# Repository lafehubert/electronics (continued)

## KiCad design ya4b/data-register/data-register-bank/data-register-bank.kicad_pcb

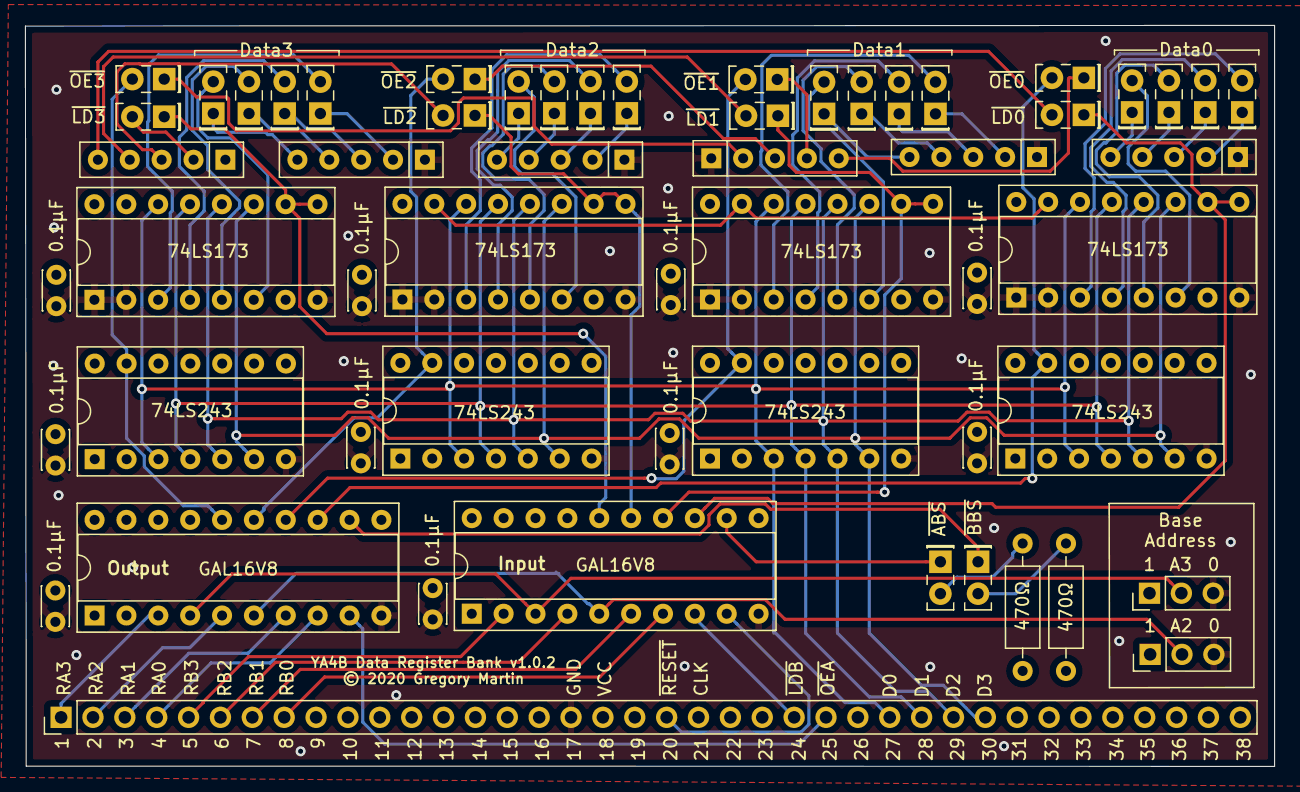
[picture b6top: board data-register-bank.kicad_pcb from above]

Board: 4 copper layers, 99.6 x 59.1 mm, 57 parts (0 on the bottom side), 73 nets.

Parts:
C1, C2, C3, C4, C5, C6, C7, C8, C9, C10: 0.1µF; C_Disc_D3.0mm_W2.0mm_P2.50mm
D1, D2, D3, D4, D5, D6, D7, D8, D9, D10, D11, D12, D13, D14, D15, D16, D17, D18, D19, D20, D21, D22, D23, D24, D25, D26: LED; LED_Rectangular_W5.0mm_H2.0mm
J1: Conn_01x38; PinHeader_1x38_P2.54mm_Vertical
JP1, JP2: Jumper_3_Bridged12; PinHeader_1x03_P2.54mm_Vertical
R1, R2: 470Ω; R_Axial_DIN0207_L6.3mm_D2.5mm_P10.16mm_Horizontal
RN1, RN2, RN3, RN4, RN5, RN6: 470Ω; R_Array_SIP5
U1, U2: GAL16V8; DIP-20_W7.62mm_Socket
U3, U5, U7, U9: 74LS243; DIP-14_W7.62mm_Socket
U4, U6, U8, U10: 74LS173; DIP-16_W7.62mm_Socket

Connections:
/Data0: J1.27, U3.3, U4.14, U5.3, U6.14, U7.3, U8.14, U9.3, U10.14
/Data1: J1.28, U3.4, U4.13, U5.4, U6.13, U7.4, U8.13, U9.4, U10.13
/Data2: J1.29, U3.5, U4.12, U5.5, U6.12, U7.5, U8.12, U9.5, U10.12
/Data3: J1.30, U3.6, U4.11, U5.6, U6.11, U7.6, U8.11, U9.6, U10.11
CLK: J1.21, U4.7, U6.7, U8.7, U10.7
D0_0: D13.2, U9.11, U10.3
D0_1: D14.2, U9.10, U10.4
D0_2: D15.2, U9.9, U10.5
D0_3: D16.2, U9.8, U10.6
D1_0: D9.2, U7.11, U8.3
D1_1: D10.2, U7.10, U8.4
D1_2: D11.2, U7.9, U8.5
D1_3: D12.2, U7.8, U8.6
D2_0: D5.2, U5.11, U6.3
D2_1: D6.2, U5.10, U6.4
D2_2: D7.2, U5.9, U6.5
D2_3: D8.2, U5.8, U6.6
D3_0: D1.2, U3.11, U4.3
D3_1: D2.2, U3.10, U4.4
D3_2: D3.2, U3.9, U4.5
D3_3: D4.2, U3.8, U4.6
GND: C1.2, C2.2, C3.2, C4.2, C5.2, C6.2, C7.2, C8.2, C9.2, C10.2, J1.17, JP1.3, JP2.3, RN1.1, RN2.1, RN3.1, RN4.1, RN6.1, U1.10, U2.10, U3.7, U4.1, U4.2, U4.8, U5.7, U6.1, U6.2, U6.8, U7.7, U8.1, U8.2, U8.8, U9.7, U10.1, U10.2, U10.8
JP2: JP2.2, U1.5, U2.6
JP3: JP1.2, U1.3, U2.4
unnamed: D1.1, RN1.2
unnamed: D2.1, RN1.3
unnamed: D3.1, RN1.4
unnamed: D4.1, RN1.5
unnamed: D5.1, RN2.2
unnamed: D6.1, RN2.3
unnamed: D7.1, RN2.4
unnamed: D8.1, RN2.5
unnamed: D9.1, RN3.2
unnamed: D10.1, RN3.3
unnamed: D11.1, RN3.4
unnamed: D12.1, RN3.5
unnamed: D13.1, RN4.2
unnamed: D14.1, RN4.3
unnamed: D15.1, RN4.4
unnamed: D16.1, RN4.5
unnamed: D17.2, RN5.2
unnamed: D18.2, RN5.3
unnamed: D19.2, RN5.4
unnamed: D20.2, RN5.5
unnamed: D21.1, RN6.2
unnamed: D22.1, RN6.3
unnamed: D23.1, RN6.4
unnamed: D24.1, RN6.5
unnamed: D25.2, R1.2
unnamed: D26.2, R2.2
OE0: D24.2, U2.13, U9.13
OE1: D23.2, U2.14, U7.13
OE2: D22.2, U2.15, U5.13
OE3: D21.2, U2.16, U3.13
RA0: J1.4, U2.8
RA1: J1.3, U2.7
RA2: J1.2, U2.5
RA3: J1.1, U2.3
RB0: J1.8, U1.7
RB1: J1.7, U1.6
RB2: J1.6, U1.4
RB3: J1.5, U1.2
RST: U1.17, U4.15, U6.15, U8.15, U10.15
VCC: C1.1, C2.1, C3.1, C4.1, C5.1, C6.1, C7.1, C8.1, C9.1, C10.1, J1.18, JP1.1, JP2.1, R1.1, R2.1, RN5.1, U1.1, U1.11, U1.20, U2.1, U2.2, U2.11, U2.20, U3.1, U3.14, U4.16, U5.1, U5.14, U6.16, U7.1, U7.14, U8.16, U9.1, U9.14, U10.16
~ABS~: D25.1, U2.12
~AOE~: J1.25, U2.9
~BBS~: D26.1, U1.12
~LD0~: D20.1, U1.13, U10.9, U10.10
~LD1~: D19.1, U1.14, U8.9, U8.10
~LD2~: D18.1, U1.15, U6.9, U6.10
~LD3~: D17.1, U1.16, U4.9, U4.10
~LDB~: J1.24, U1.8
~RESET~: J1.20, U1.9

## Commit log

2019-12-07 Adding slow-clock module for ya4b
2019-12-26 Adding YA4b stuff
2019-12-26 Cleanup up unnecessary files
2019-12-28 Transfer register changes; address register initial check-in
2019-12-30 First cut at address register; checking in, but design is wrong; need 74LS169 chips for this.
2020-01-24 New address register bits.
2020-02-15 Added transfer-register Added address-register Added data-register Fixed a mislabeling on ram board.
2020-02-15 Added second register address bus; forgot it in previous revision
2020-02-22 Adding data register schematics; updated a few things, too.
2020-03-11 Updated schematic and pcb for data register bank; data pins were off by one
2020-03-11 New library for testing YA4B CPU modules
2020-03-11 Rewrote transfer register tests using the test library
2020-03-11 Rearranging directories in address-register-control
2020-03-11 Splitting the tests apart for address-register-control
2020-03-13 Refactored address-register-control tests
2020-03-13 Rearranging data register control design files
2020-03-14 Data register control tests are done, and functional.
2020-04-11 Adding tests; fixed PCB design files
2020-04-11 Fixed PCB design files for address register bank
2020-04-27 Made a patched version of the data register bank output control GAL because of an error on the PCB design.
    Created a design for the ALU in Digital that seems to work.
2020-06-12 Finished ALU simulation/design; all breadboarded; ready for PCB design
2022-01-08 Updated designs and simulations
